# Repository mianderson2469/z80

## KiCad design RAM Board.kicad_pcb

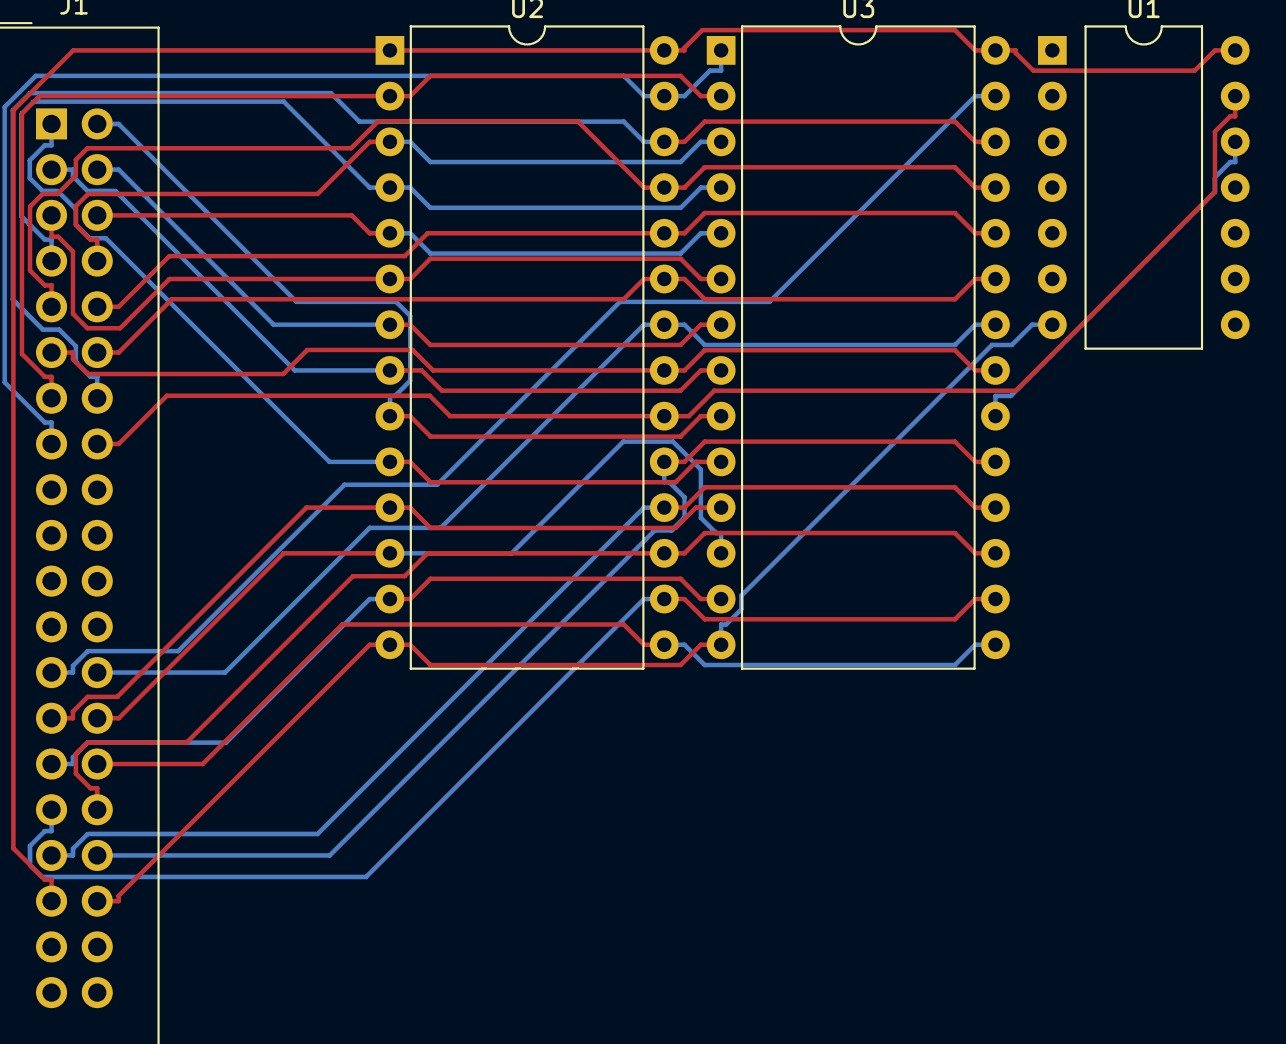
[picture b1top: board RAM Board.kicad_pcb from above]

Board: 2 copper layers, 4 parts (0 on the bottom side), 29 nets.

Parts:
J1: Conn_02x20_Odd_Even; IDC-Header_2x20_P2.54mm_Vertical
U1: SN74LS04N; DIP-14_W10.16mm
U2: 27C256; DIP-28_W15.24mm
U3: KM62256D; DIP-28_W15.24mm

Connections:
unnamed: J1.1, U2.10, U3.10
unnamed: J1.2, U2.9, U3.9
unnamed: J1.3, U2.8, U3.8
unnamed: J1.4, U2.7, U3.7
unnamed: J1.5, U2.6, U3.6
unnamed: J1.6, U2.5, U3.5
unnamed: J1.7, U2.4, U3.4
unnamed: J1.8, U2.3, U3.3
unnamed: J1.9, U2.25, U3.25
unnamed: J1.10, U2.24, U3.24
unnamed: J1.11, U2.21, U3.21
unnamed: J1.12, U2.23, U3.23
unnamed: J1.13, U2.2, U3.2
unnamed: J1.14, U2.26, U3.26
unnamed: J1.15, U2.27, U3.1
unnamed: J1.16, U1.13, U2.20
unnamed: J1.25, U3.27
unnamed: J1.26, U2.22, U3.22
unnamed: J1.27, U2.11, U3.11
unnamed: J1.28, U2.12, U3.12
unnamed: J1.29, U2.13, U3.13
unnamed: J1.30, U2.15, U3.15
unnamed: J1.31, U2.16, U3.16
unnamed: J1.32, U2.17, U3.17
unnamed: J1.33, U2.18, U3.18
unnamed: J1.34, U2.19, U3.19
unnamed: J1.35, U1.14, U2.1, U2.28, U3.28
unnamed: J1.36, U1.7, U2.14, U3.14
unnamed: U1.12, U3.20

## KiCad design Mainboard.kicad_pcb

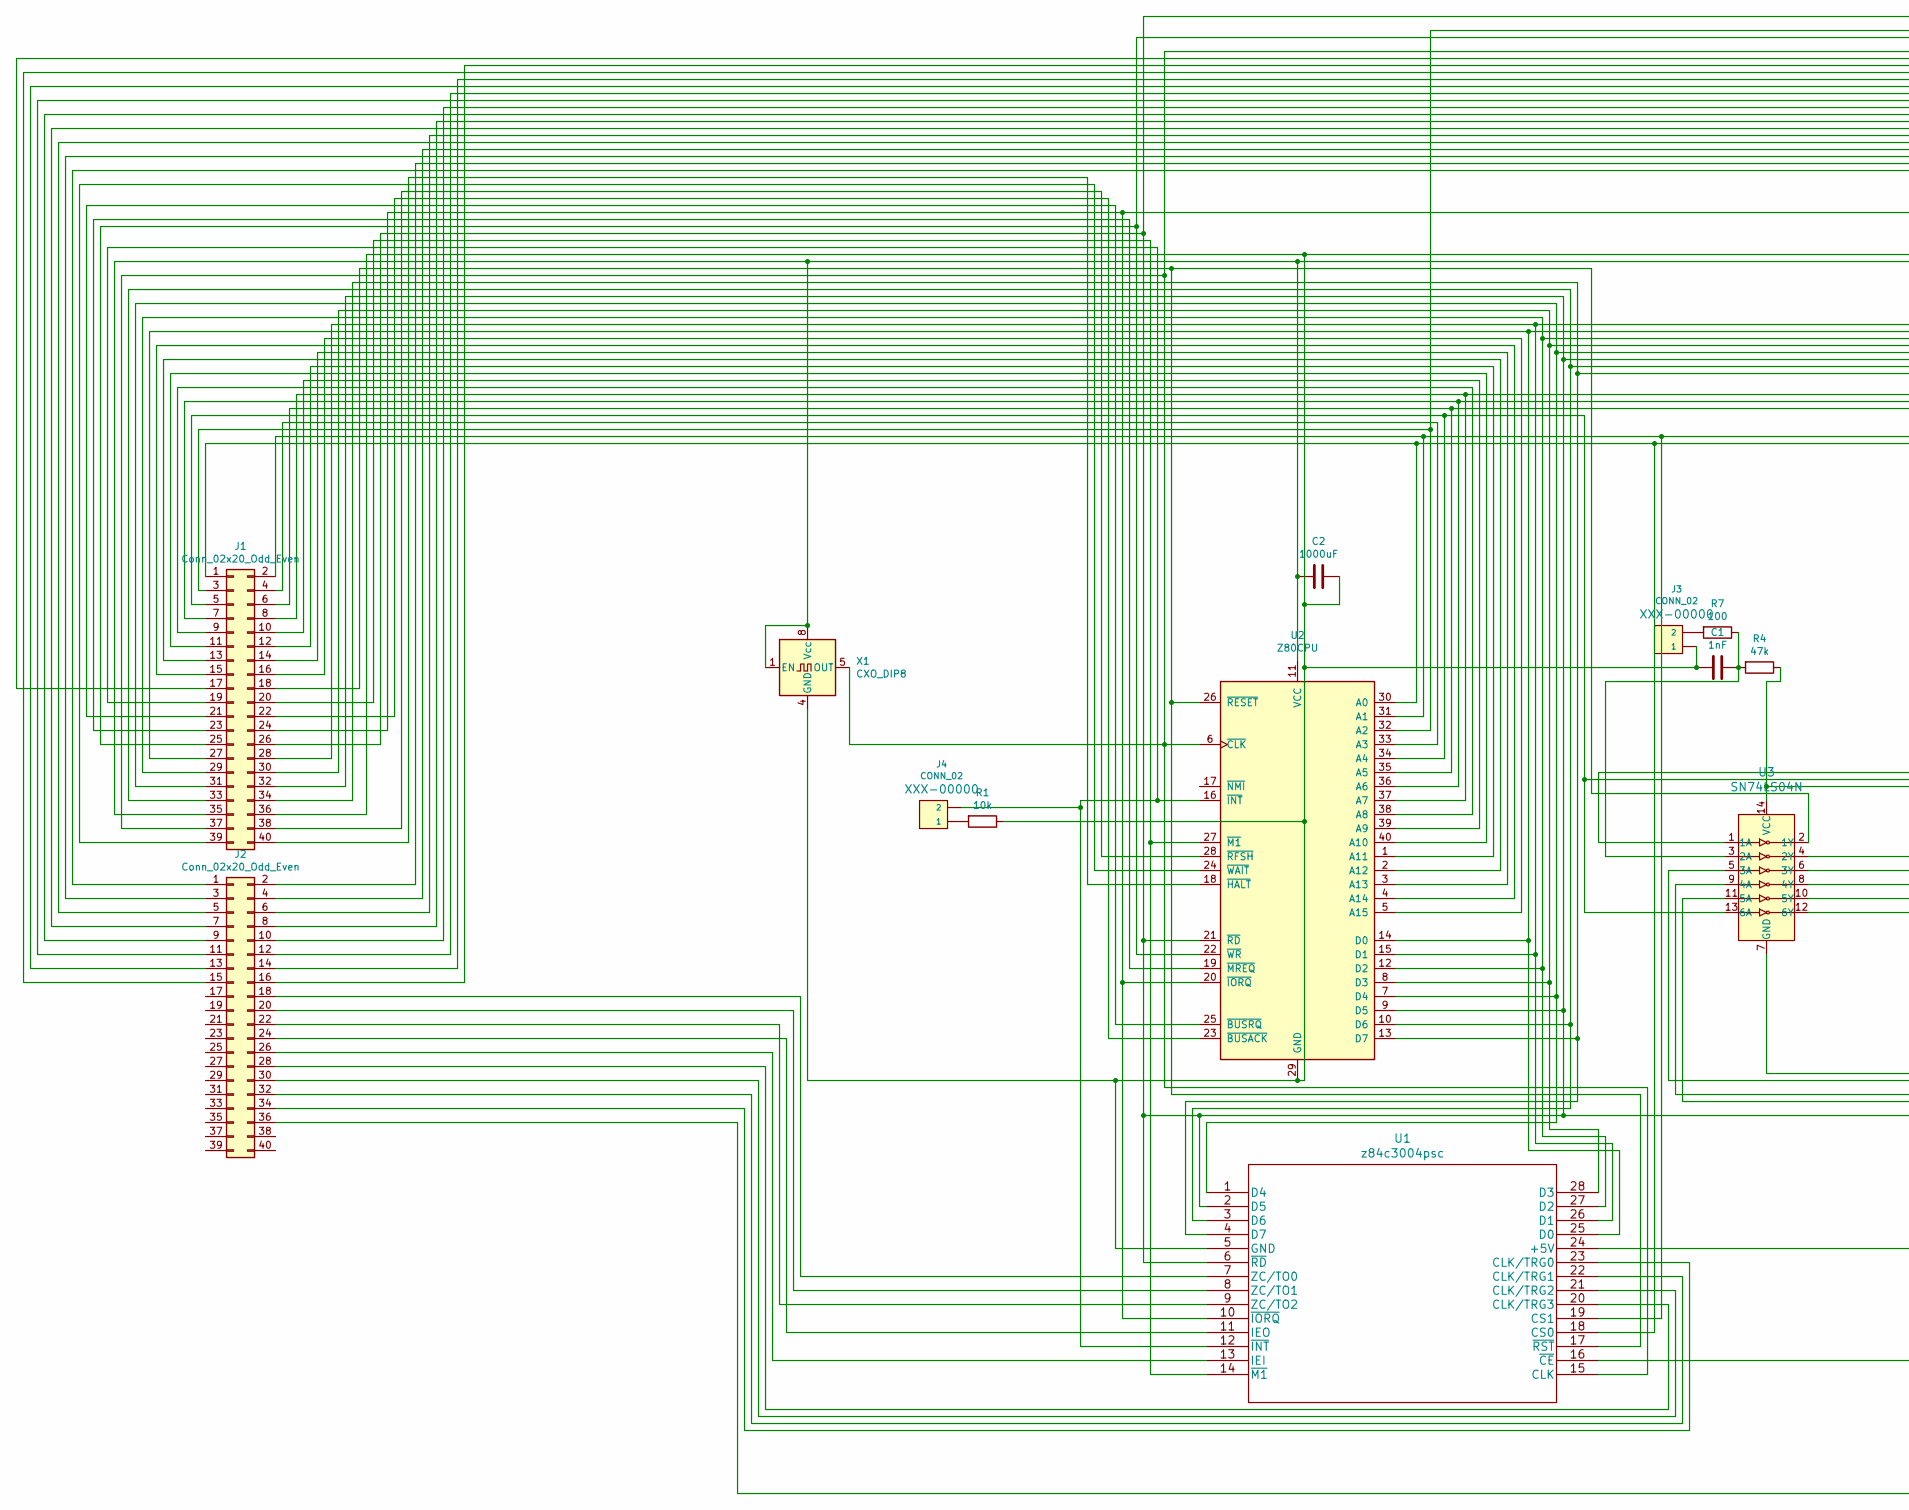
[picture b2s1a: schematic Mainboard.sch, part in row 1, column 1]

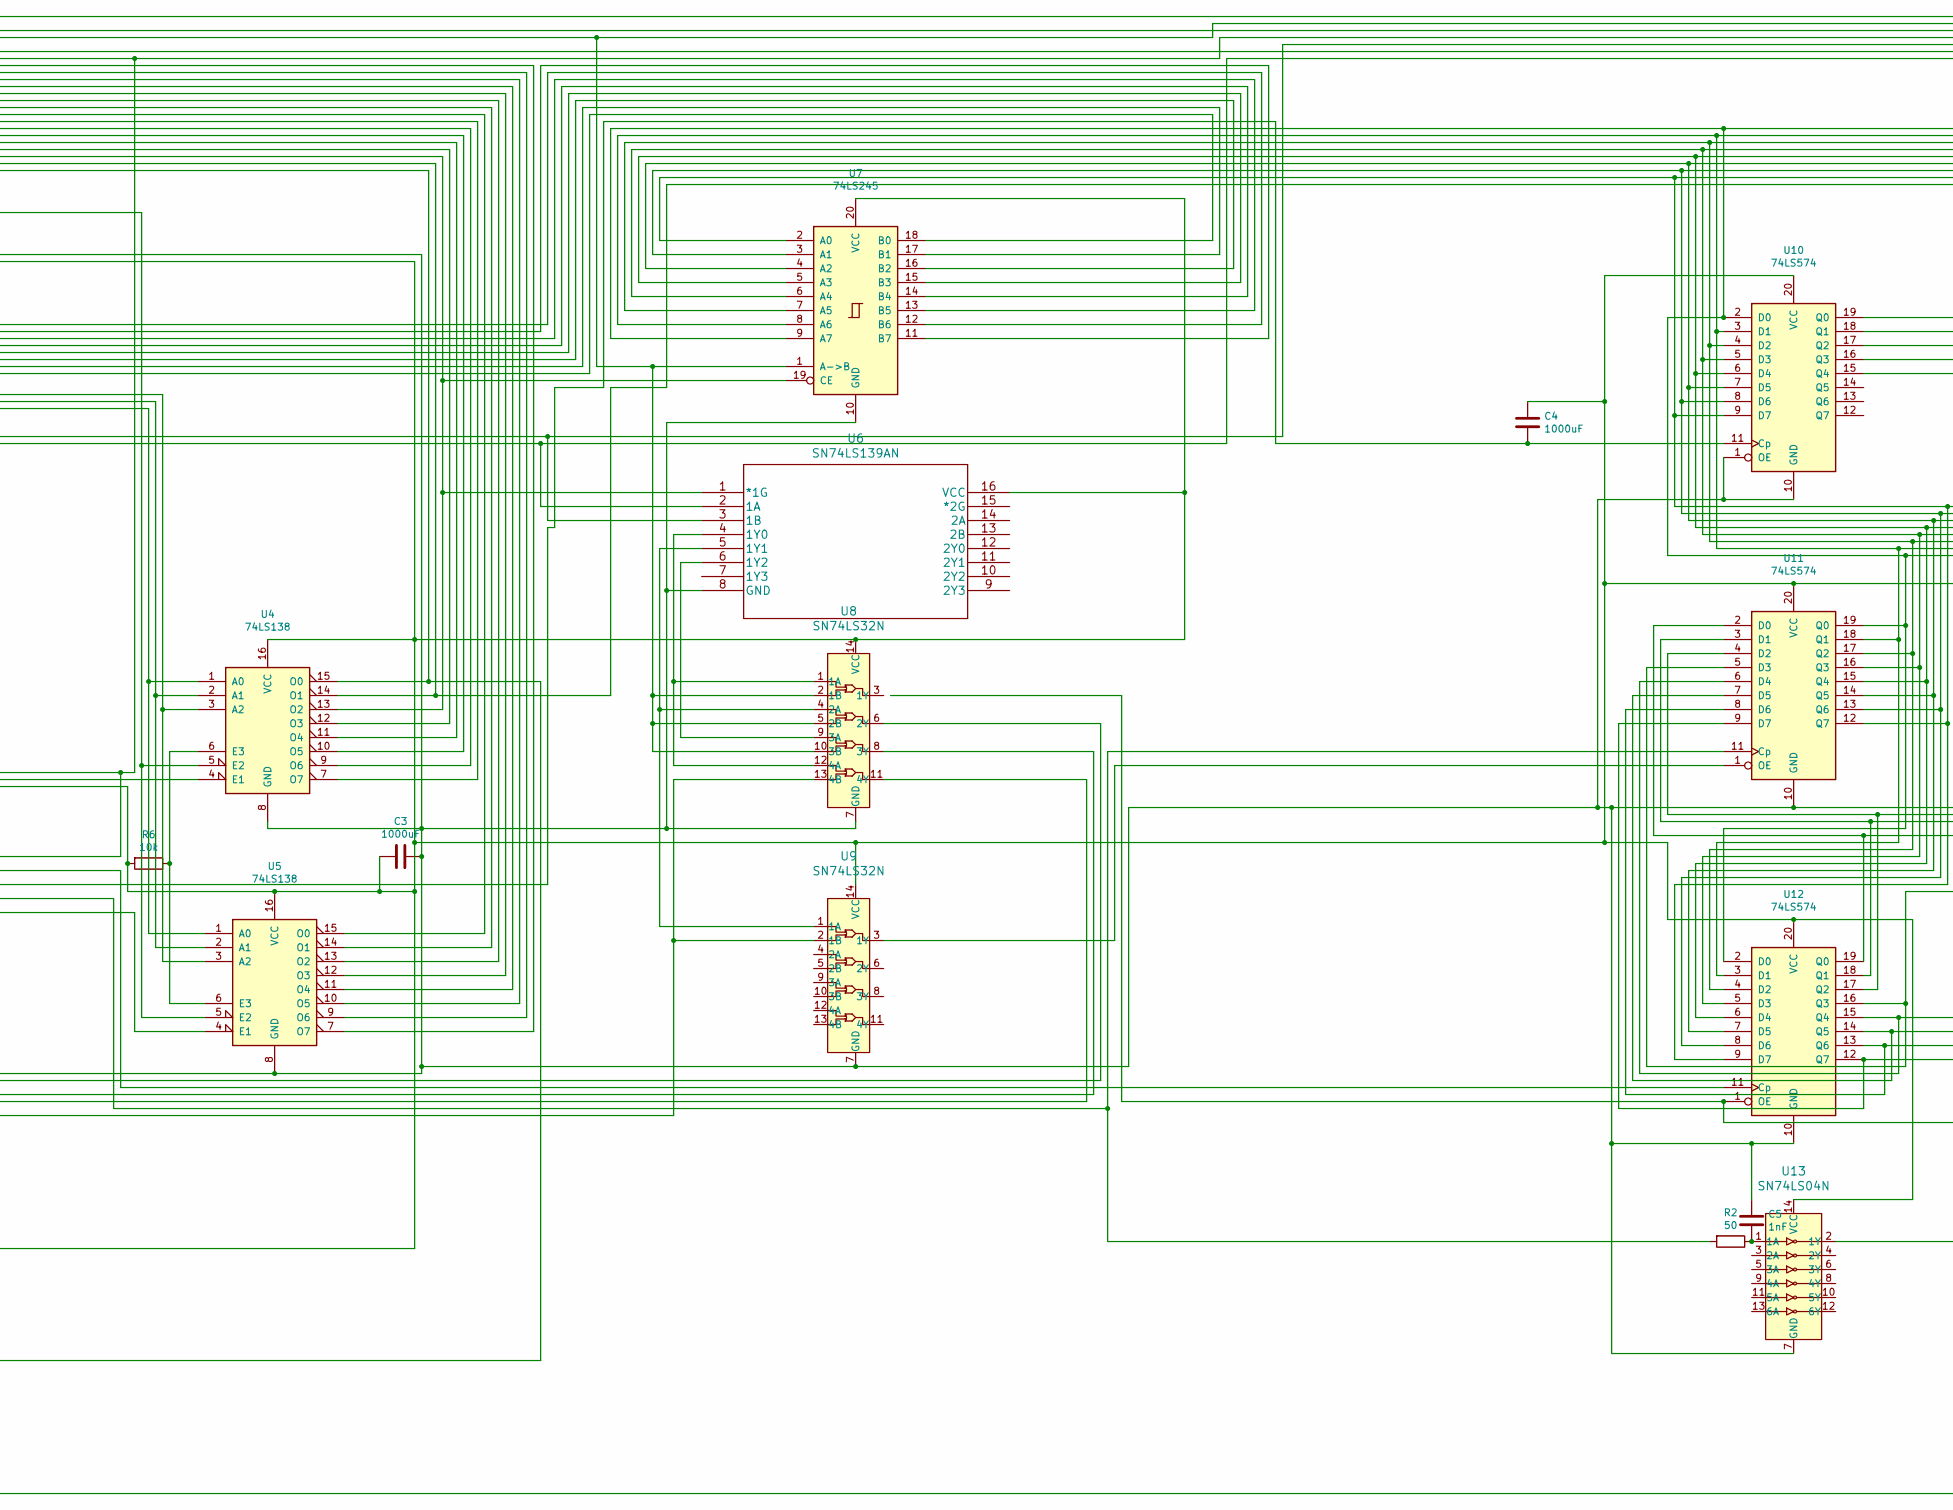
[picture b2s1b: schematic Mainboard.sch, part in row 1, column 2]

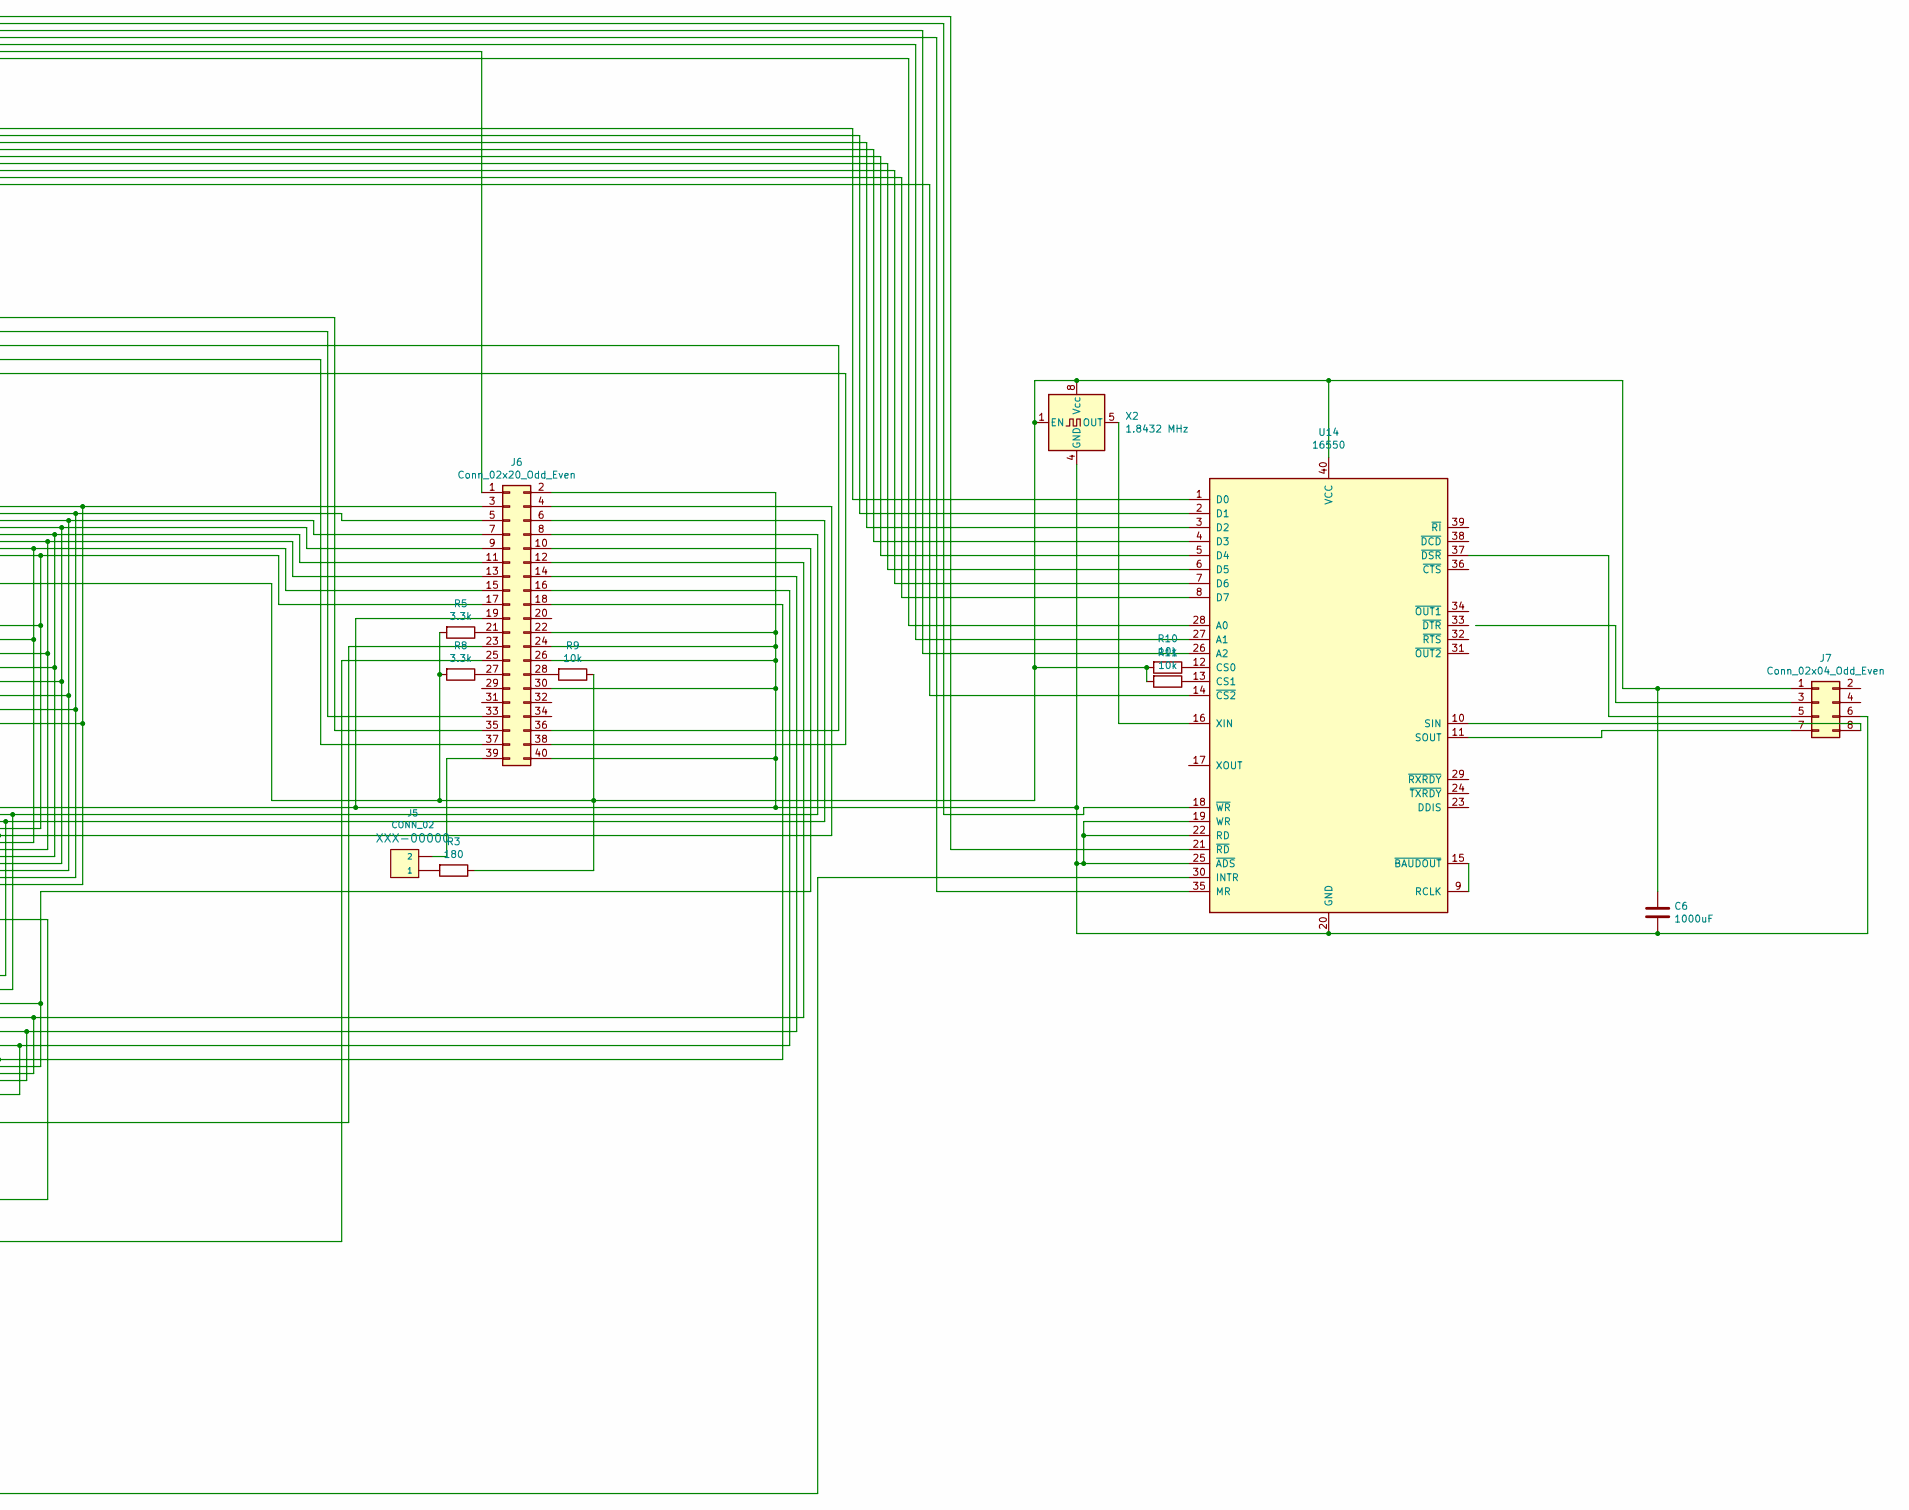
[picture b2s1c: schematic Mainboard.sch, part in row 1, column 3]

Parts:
C1, C5: 1nF; CP_Radial_D4.0mm_P1.50mm
C2, C3, C4, C6: 1000uF; CP_Radial_D4.0mm_P1.50mm
J1, J2, J6: Conn_02x20_Odd_Even; IDC-Header_2x20_P2.54mm_Vertical
J3, J4, J5: CONN_02; 1X02
J7: Conn_02x04_Odd_Even; JST_PHD_B8B-PHDSS_2x04_P2.00mm_Vertical
R1: 10k; R_Axial_DIN0207_L6.3mm_D2.5mm_P10.16mm_Horizontal
R2: 50; R_Axial_DIN0207_L6.3mm_D2.5mm_P10.16mm_Horizontal
R3: 180; R_Axial_DIN0207_L6.3mm_D2.5mm_P10.16mm_Horizontal
R4: 47k; R_Axial_DIN0204_L3.6mm_D1.6mm_P7.62mm_Horizontal
R5: 3.3k; R_Axial_DIN0207_L6.3mm_D2.5mm_P10.16mm_Horizontal
R6, R9, R10, R11: 10k; R_Axial_DIN0204_L3.6mm_D1.6mm_P7.62mm_Horizontal
R7: 100; R_Axial_DIN0204_L3.6mm_D1.6mm_P7.62mm_Horizontal
R8: 3.3k; R_Axial_DIN0204_L3.6mm_D1.6mm_P7.62mm_Horizontal
U1: z84c3004psc
U2: Z80CPU; DIP_Socket-40_W11.9_W12.7_W15.24_W17.78_W18.5_3M_240-1280-0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
U3: SN74LS04N; DIP14; MPN SN74LS04N; Digi-Key_PN 296-1629-5-ND
U4, U5: 74LS138; DIP-16_W10.16mm
U6: SN74LS139AN; DIP16
U7: 74LS245; DIP-20_W7.62mm
U8, U9: SN74LS32N; DIP14-KIT; MPN SN74LS32N; Digi-Key_PN 296-1658-5-ND
U10, U11, U12: 74LS574; DIP-20_W7.62mm_Socket
U13: SN74LS04N; DIP-14_W7.62mm; MPN SN74LS04N; Digi-Key_PN 296-1629-5-ND
U14: 16550; DIP-40_W15.24mm
X1: CXO_DIP8; Oscillator_DIP-8
X2: 1.8432 MHz; Oscillator_DIP-8

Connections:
unnamed: C1.1, R4.2, R7.1, U3.3 (2A)
unnamed: C1.2, C2.1, C3.1, C5.1, C6.2, J1.36, J3.1, J6.2, J6.19, J6.22, J6.24, J6.26, J6.30, J6.40, J7.6, R1.1, U1.5 (GND), U2.29 (GND), U3.7 (GND), U4.8 (GND), U5.8 (GND), U6.8 (GND), U7.10 (GND), U8.7 (GND), U9.7 (GND), U10.1 (OE), U10.10 (GND), U11.10 (GND), U12.10 (GND), U13.7 (GND), U14.19 (WR), U14.20 (GND), U14.22 (RD), U14.25 (~ADS~), X1.4 (GND), X2.4 (GND)
unnamed: C2.2, C3.2, C4.1, C6.1, J1.35, J7.1, R3.1, R4.1, R5.2, R6.2, R8.2, R9.1, R10.2, R11.2, U1.24 (+5V), U2.11 (VCC), U3.14 (VCC), U4.16 (VCC), U5.16 (VCC), U6.16 (VCC), U7.20 (VCC), U8.14 (VCC), U9.14 (VCC), U10.20 (VCC), U11.20 (VCC), U12.20 (VCC), U13.14 (VCC), U14.40 (VCC), X1.1 (EN), X1.8 (Vcc), X2.1 (EN), X2.8 (Vcc)
unnamed: C4.2, U3.8 (4Y), U10.11 (Cp)
unnamed: C5.2, R2.1, U13.1 (1A)
unnamed: J1.1, U1.18 (CS0), U2.30 (A0), U6.2 (1A), U14.28 (A0)
unnamed: J1.2, U1.19 (CS1), U2.31 (A1), U6.3 (1B), U14.27 (A1)
unnamed: J1.3, U2.32 (A2), U14.26 (A2)
unnamed: J1.4, U2.33 (A3)
unnamed: J1.5, U2.34 (A4), U3.13 (6A), U4.4 (E1)
unnamed: J1.6, U2.35 (A5), U4.1 (A0), U5.1 (A0)
unnamed: J1.7, U2.36 (A6), U4.2 (A1), U5.2 (A1)
unnamed: J1.8, U2.37 (A7), U4.3 (A2), U5.3 (A2)
unnamed: J1.9, U2.38 (A8)
unnamed: J1.10, U2.39 (A9)
unnamed: J1.11, U2.40 (A10)
unnamed: J1.12, U2.1 (A11)
unnamed: J1.13, U2.2 (A12)
unnamed: J1.14, U2.3 (A13)
unnamed: J1.15, U2.4 (A14)
unnamed: J1.16, U2.5 (A15)
unnamed: J1.17, U3.1 (1A), U3.4 (2Y), U14.35 (MR)
unnamed: J1.18, U1.17 (~RST), U2.26 (~RESET~), U3.2 (1Y)
unnamed: J1.19, J4.2, U1.12 (~INT), U2.16 (~INT~)
unnamed: J1.20, U1.14 (~M1), U2.27 (~M1~)
unnamed: J1.21, U2.25 (~BUSRQ~)
unnamed: J1.22, U2.23 (~BUSACK~)
unnamed: J1.23, U2.19 (~MREQ~)
unnamed: J1.24, U1.10 (~IORQ), U2.20 (~IORQ~), U4.5 (E2), U5.5 (E2)
unnamed: J1.25, U2.22 (~WR~), U7.1 (A->B), U8.2 (1B), U8.5 (2B), U8.10 (3B), U14.18 (~WR~)
unnamed: J1.26, J1.32, U1.2 (D5), U1.6 (~RD), U2.9 (D5), U2.21 (~RD~), U7.16 (B2), U8.13 (4B), U9.2 (1B), U14.21 (~RD~)
unnamed: J1.27, U1.25 (D0), U2.14 (D0), U7.11 (B7)
unnamed: J1.28, U1.26 (D1), U2.15 (D1), U7.12 (B6)
unnamed: J1.29, U1.27 (D2), U2.12 (D2), U7.13 (B5)
unnamed: J1.30, U1.28 (D3), U2.8 (D3), U7.14 (B4)
unnamed: J1.31, U1.1 (D4), U2.7 (D4), U7.15 (B3)
unnamed: J1.33, U1.3 (D6), U2.10 (D6), U7.17 (B1)
unnamed: J1.34, U1.4 (D7), U2.13 (D7), U7.18 (B0)
unnamed: J1.37, J6.1, U1.15 (CLK), U2.6 (~CLK~), X1.5 (OUT)
unnamed: J1.38, U2.28 (~RFSH~)
unnamed: J1.39, U2.24 (~WAIT~)
unnamed: J1.40, U2.18 (~HALT~)
unnamed: J2.1, U1.16 (~CE), U4.15 (O0)
unnamed: J2.2, U4.14 (O1), U14.14 (~CS2~)
unnamed: J2.3, U4.13 (O2), U6.1 (*1G), U7.19 (CE)
unnamed: J2.4, U4.12 (O3)
unnamed: J2.5, U4.11 (O4)
unnamed: J2.6, U4.10 (O5)
unnamed: J2.7, U4.9 (O6)
unnamed: J2.8, U4.7 (O7)
unnamed: J2.9, U5.15 (O0)
unnamed: J2.10, U5.14 (O1)
unnamed: J2.11, U5.13 (O2)
unnamed: J2.12, U5.12 (O3)
unnamed: J2.13, U5.11 (O4)
unnamed: J2.14, U5.10 (O5)
unnamed: J2.15, U5.9 (O6)
unnamed: J2.16, U5.7 (O7)
unnamed: J2.18, U1.7 (ZC/TO0)
unnamed: J2.20, U1.8 (ZC/TO1)
unnamed: J2.22, U1.9 (ZC/TO2)
unnamed: J2.24, U1.11 (IEO)
unnamed: J2.26, U1.13 (IEI)
unnamed: J2.28, U1.20 (CLK/TRG3)
unnamed: J2.30, U1.21 (CLK/TRG2)
unnamed: J2.32, U1.22 (CLK/TRG1)
unnamed: J2.34, U1.23 (CLK/TRG0)
unnamed: J2.36, U14.30 (INTR)
unnamed: J3.2, R7.2
unnamed: J4.1, R1.2
unnamed: J5.1, R3.2
unnamed: J5.2, J6.39
unnamed: J6.3, U7.2 (A0), U10.9 (D7), U11.12 (Q7), U12.9 (D7), U14.8 (D7)
unnamed: J6.4, U11.2 (D0), U12.19 (Q0)
unnamed: J6.5, U7.3 (A1), U10.8 (D6), U11.13 (Q6), U12.8 (D6), U14.7 (D6)
unnamed: J6.6, U11.3 (D1), U12.18 (Q1)
unnamed: J6.7, U7.4 (A2), U10.7 (D5), U11.14 (Q5), U12.7 (D5), U14.6 (D5)
unnamed: J6.8, U11.4 (D2), U12.17 (Q2)
unnamed: J6.9, U7.5 (A3), U10.6 (D4), U11.15 (Q4), U12.6 (D4), U14.5 (D4)
unnamed: J6.10, U11.5 (D3), U12.16 (Q3)
unnamed: J6.11, U7.6 (A4), U10.5 (D3), U11.16 (Q3), U12.5 (D3), U14.4 (D3)
unnamed: J6.12, U11.6 (D4), U12.15 (Q4)
unnamed: J6.13, U7.7 (A5), U10.4 (D2), U11.17 (Q2), U12.4 (D2), U14.3 (D2)
unnamed: J6.14, U11.7 (D5), U12.14 (Q5)
unnamed: J6.15, U7.8 (A6), U10.3 (D1), U11.18 (Q1), U12.3 (D1), U14.2 (D1)
unnamed: J6.16, U11.8 (D6), U12.13 (Q6)
unnamed: J6.17, U7.9 (A7), U10.2 (D0), U11.19 (Q0), U12.2 (D0), U14.1 (D0)
unnamed: J6.18, U11.9 (D7), U12.12 (Q7)
unnamed: J6.21, R5.1
unnamed: J6.23, U12.1 (OE)
unnamed: J6.25, U13.2 (1Y)
unnamed: J6.27, R8.1
unnamed: J6.28, R9.2
unnamed: J6.33, U10.18 (Q1)
unnamed: J6.35, U10.19 (Q0)
unnamed: J6.36, U10.17 (Q2)
unnamed: J6.37, U10.16 (Q3)
unnamed: J6.38, U10.15 (Q4)
unnamed: J7.5, U14.37 (~DSR~)
unnamed: J7.7, U14.11 (SOUT)
unnamed: J7.8, U14.10 (SIN)
unnamed: R2.2, U3.10 (5Y), U11.11 (Cp)
unnamed: R6.1, U4.6 (E3), U5.6 (E3)
unnamed: R10.1, U14.12 (CS0)
unnamed: R11.1, U14.13 (CS1)
unnamed: U3.5 (3A), U8.6 (2Y)
unnamed: U3.9 (4A), U8.8 (3Y)
unnamed: U3.11 (5A), U8.11 (4Y)
unnamed: U3.12 (6Y), U5.4 (E1)
unnamed: U6.4 (1Y0), U8.1 (1A), U8.12 (4A)
unnamed: U6.5 (1Y1), U8.4 (2A), U9.1 (1A)
unnamed: U6.6 (1Y2), U8.9 (3A)
unnamed: U9.3 (1Y), U11.1 (OE)
unnamed: U3.6 (3Y), U12.11 (Cp)
unnamed: U14.9 (RCLK), U14.15 (~BAUDOUT~)
unnamed: U14.16 (XIN), X2.5 (OUT)

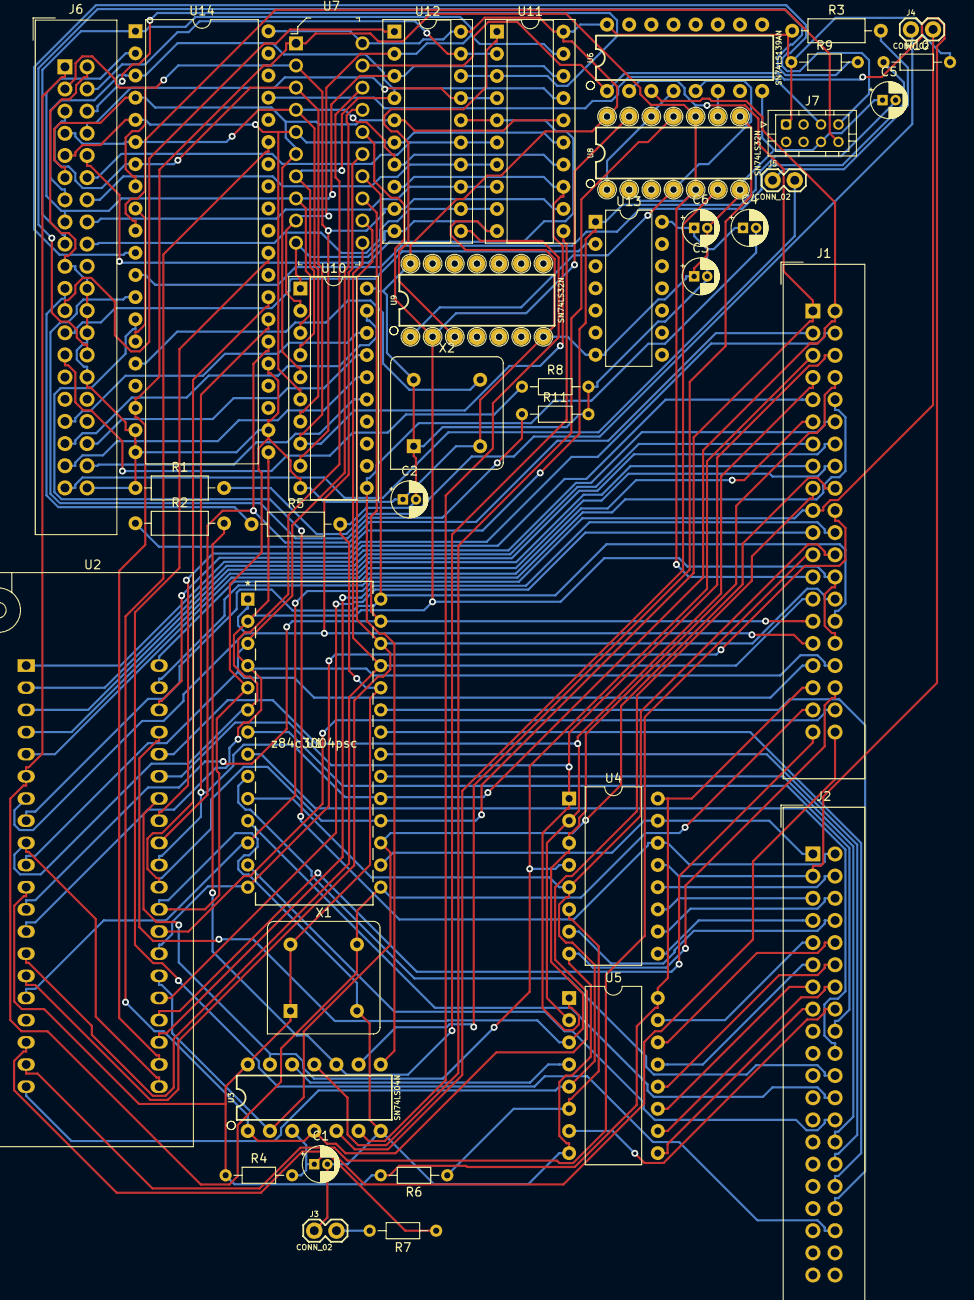
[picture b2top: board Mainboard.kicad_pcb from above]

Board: 2 copper layers, 40 parts (0 on the bottom side), 116 nets.

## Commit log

2019-05-30 Create z80 Monitor
2019-05-31 Update z80 Monitor
2019-05-31 Add revised monitor source code.

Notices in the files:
parts and their libraries:
Copyright 2016 Accelerated Designs. All rights reserved.
